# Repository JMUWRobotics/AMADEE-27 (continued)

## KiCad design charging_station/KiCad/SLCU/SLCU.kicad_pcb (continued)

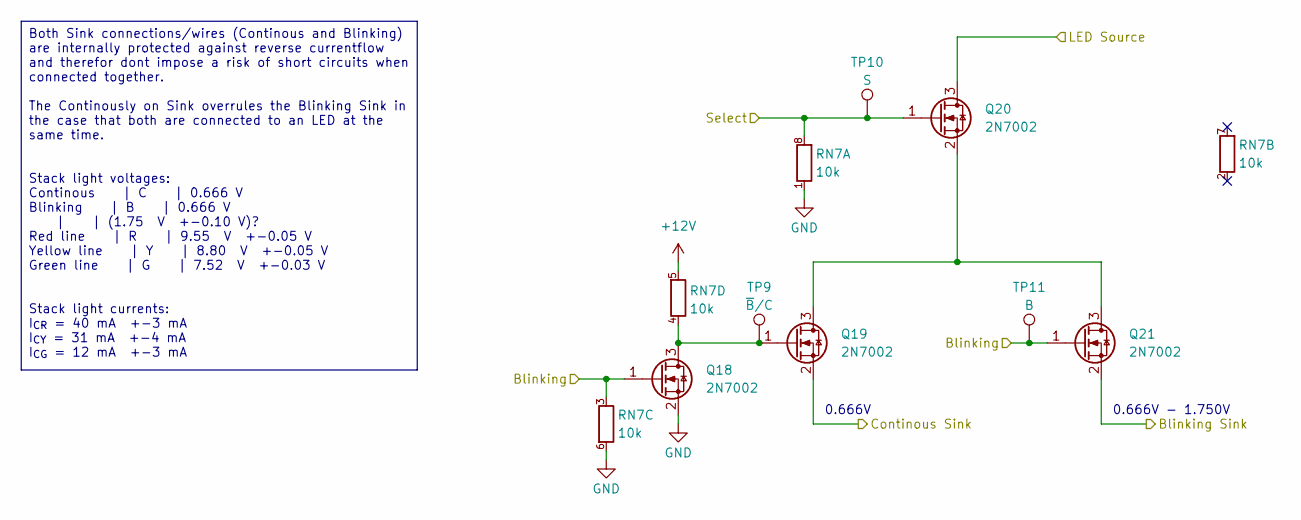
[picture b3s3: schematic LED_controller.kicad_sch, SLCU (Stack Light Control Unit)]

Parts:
Q18, Q19, Q20, Q21: 2N7002; SOT-323_SC-70
RN7: 10k; RES-ARRAY-SMD_0603-8P-L3.2-W1.6-BL; MPN 4D03WGJ0103T5E; LCSC Part C29718
TP9: ~{B}/C; TestPoint_Pad_D1.0mm
TP10: S; TestPoint_Pad_D1.0mm
TP11: B; TestPoint_Pad_D1.0mm

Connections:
+12V: RN7.5 (R4.2); also elsewhere on the board
/Blinking: Q21.2 (S); also elsewhere on the board
/Continous: Q19.2 (S); also elsewhere on the board
/Raspberry Signal & Logic Multiplexing/B_RED: Q18.1 (G), Q21.1 (G), RN7.3 (R3.1), TP11.1 (1_1); also elsewhere on the board
/Raspberry Signal & Logic Multiplexing/S_RED: Q20.1 (G), RN7.8 (R1.2), TP10.1 (1_1); also elsewhere on the board
/Red: Q20.3 (D); also elsewhere on the board
GND: Q18.2 (S), RN7.1 (R1.1), RN7.6 (R3.2); also elsewhere on the board
unnamed: Q18.3 (D), Q19.1 (G), RN7.4 (R4.1), TP9.1 (1_1)
unnamed: Q19.3 (D), Q20.2 (S), Q21.3 (D)

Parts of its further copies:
Q22, Q23, Q24, Q25, Q26, Q27, Q28, Q29: 2N7002; SOT-323_SC-70
RN8, RN9: 10k; RES-ARRAY-SMD_0603-8P-L3.2-W1.6-BL; MPN 4D03WGJ0103T5E; LCSC Part C29718
TP12, TP15: ~{B}/C; TestPoint_Pad_D1.0mm
TP13, TP16: S; TestPoint_Pad_D1.0mm
TP14, TP17: B; TestPoint_Pad_D1.0mm

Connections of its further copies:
+12V: RN8.5 (R4.2), RN9.5 (R4.2); also elsewhere on the board
/Blinking: Q25.2 (S), Q29.2 (S); also elsewhere on the board
/Continous: Q23.2 (S), Q27.2 (S); also elsewhere on the board
/Green: Q28.3 (D); also elsewhere on the board
/Green Light Driver/Blinking: Q26.1 (G), Q29.1 (G), RN9.3 (R3.1), TP17.1 (1_1); also elsewhere on the board
/Green Light Driver/Select: Q28.1 (G), RN9.8 (R1.2), TP16.1 (1_1); also elsewhere on the board
/Raspberry Signal & Logic Multiplexing/B_YELLOW: Q22.1 (G), Q25.1 (G), RN8.3 (R3.1), TP14.1 (1_1); also elsewhere on the board
/Raspberry Signal & Logic Multiplexing/S_YELLOW: Q24.1 (G), RN8.8 (R1.2), TP13.1 (1_1); also elsewhere on the board
/Yellow: Q24.3 (D); also elsewhere on the board
GND: Q22.2 (S), Q26.2 (S), RN8.1 (R1.1), RN8.6 (R3.2), RN9.1 (R1.1), RN9.6 (R3.2); also elsewhere on the board
unnamed: Q22.3 (D), Q23.1 (G), RN8.4 (R4.1), TP12.1 (1_1)
unnamed: Q23.3 (D), Q24.2 (S), Q25.3 (D)
unnamed: Q26.3 (D), Q27.1 (G), RN9.4 (R4.1), TP15.1 (1_1)
unnamed: Q27.3 (D), Q28.2 (S), Q29.3 (D)

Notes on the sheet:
0.666V
0.666V - 1.750V
Both Sink connections/wires (Continous and Blinking) are internally protected against reverse currentflow and therefor dont impose a risk of short circuits when connected together. The Continously on Sink overrules the Blinking Sink in the case that both are connected to an LED at the same time. St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

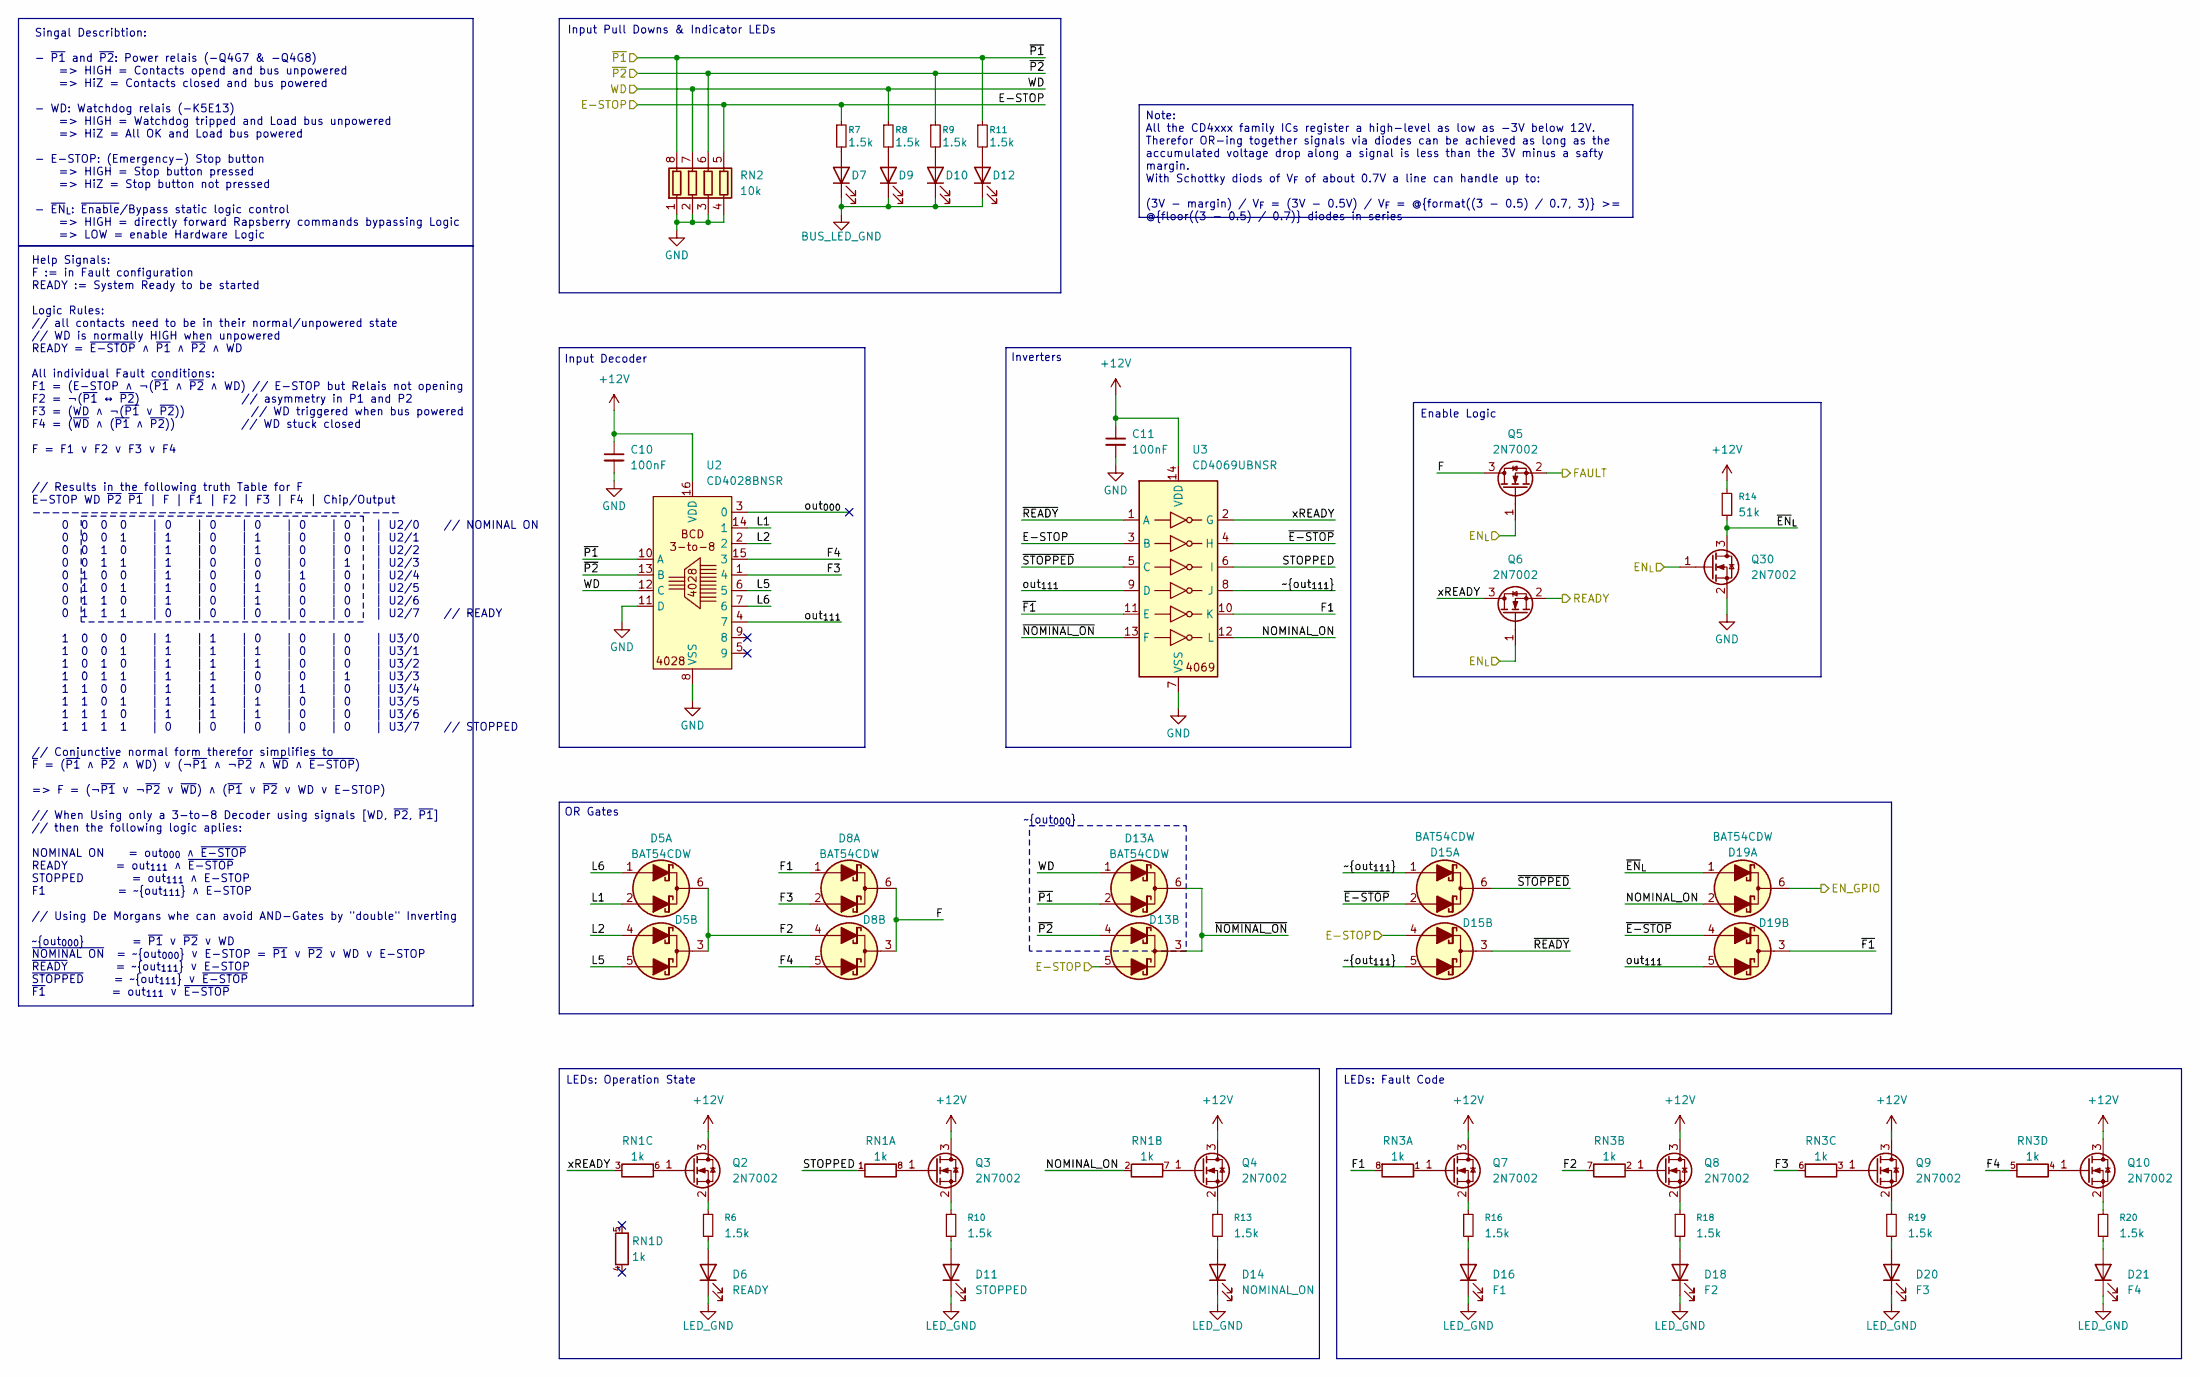
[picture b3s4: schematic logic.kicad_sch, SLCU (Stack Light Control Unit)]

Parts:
C10, C11: 100nF; C_0805_2012Metric_Pad1.18x1.45mm_HandSolder
D5, D8, D13, D15, D19: BAT54CDW; SOT-363_SC-70-6
D6: READY; LED_0805_2012Metric_Pad1.15x1.40mm_HandSolder
D7: E-STOP; LED_0805_2012Metric_Pad1.15x1.40mm_HandSolder
D9: WD; LED_0805_2012Metric_Pad1.15x1.40mm_HandSolder
D10: ~{P2}; LED_0805_2012Metric_Pad1.15x1.40mm_HandSolder
D11: STOPPED; LED_0805_2012Metric_Pad1.15x1.40mm_HandSolder
D12: ~{P1}; LED_0805_2012Metric_Pad1.15x1.40mm_HandSolder
D14: NOMINAL_ON; LED_0805_2012Metric_Pad1.15x1.40mm_HandSolder
D16: F1; LED_0805_2012Metric_Pad1.15x1.40mm_HandSolder
D18: F2; LED_0805_2012Metric_Pad1.15x1.40mm_HandSolder
D20: F3; LED_0805_2012Metric_Pad1.15x1.40mm_HandSolder
D21: F4; LED_0805_2012Metric_Pad1.15x1.40mm_HandSolder
Q2, Q3, Q4, Q5, Q6, Q7, Q8, Q9, Q10, Q30: 2N7002; SOT-323_SC-70
R6, R7, R8, R9, R10, R11, R13, R16, R18, R19, R20: 1.5k; R_0805_2012Metric_Pad1.20x1.40mm_HandSolder
R14: 51k; R_0805_2012Metric_Pad1.20x1.40mm_HandSolder
RN1, RN3: 1k; RES-ARRAY-SMD_0603-8P-L3.2-W1.6-BL; MPN 4D03WGJ0102T5E; LCSC Part C20197
RN2: 10k; RES-ARRAY-SMD_0603-8P-L3.2-W1.6-BL; MPN 4D03WGJ0103T5E; LCSC Part C29718
U2: CD4028BNSR; SOIC127P780X200-16N; MPN CD4028BNSR; LCSC Part C2869122
U3: CD4069UBNSR; SOIC127P780X200-14N; Mouser Part Number 595-CD4069UBNSR

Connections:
+12V: C10.1, C11.1, Q2.3 (D), Q3.3 (D), Q4.3 (D), Q7.3 (D), Q8.3 (D), Q9.3 (D), Q10.3 (D), R14.1, U2.16 (VDD), U3.14 (VDD); also elsewhere on the board
/E-STOP: D13.5 (A2), D15.4 (A2), R7.1, RN2.5 (R4.2), U3.3 (B); also elsewhere on the board
/Logic/EN_GPIO: D19.6 (K1); also elsewhere on the board
/Logic/EN_{L}: Q5.1 (G), Q6.1 (G), Q30.1 (G); also elsewhere on the board
/Logic/F: D8.3 (K2), D8.6 (K1), Q5.3 (D)
/Logic/F1: D8.1 (A1), RN3.8 (R1.2), U3.10 (K)
/Logic/F2: D5.3 (K2), D5.6 (K1), D8.4 (A2), RN3.7 (R2.2)
/Logic/F3: D8.2 (A1), RN3.6 (R3.2), U2.1 (4)
/Logic/F4: D8.5 (A2), RN3.5 (R4.2), U2.15 (3)
/Logic/FAULT: Q5.2 (S); also elsewhere on the board
/Logic/L1: D5.2 (A1), U2.14 (1)
/Logic/L2: D5.4 (A2), U2.2
/Logic/L5: D5.5 (A2), U2.6 (5)
/Logic/L6: D5.1 (A1), U2.7 (6)
/Logic/NOMINAL_ON: D19.2 (A1), RN1.2 (R2.1), U3.12 (L)
/Logic/READY: Q6.2 (S); also elsewhere on the board
/Logic/STOPPED: RN1.1 (R1.1), U3.6 (I)
/Logic/out_{000}: U2.3 (0)
/Logic/out_{111}: D19.5 (A2), U2.4 (7), U3.9 (D)
/Logic/xREADY: Q6.3 (D), RN1.3 (R3.1), U3.2 (G)
/Logic/~E-STOP: D15.2 (A1), D19.4 (A2), U3.4 (H)
/Logic/~EN_{L}: D19.1 (A1), Q30.3 (D), R14.2
/Logic/~F1: D19.3 (K2), U3.11 (E)
/Logic/~NOMINAL_ON: D13.3 (K2), D13.6 (K1), U3.13 (F)
/Logic/~READY: D15.3 (K2), U3.1 (A)
/Logic/~STOPPED: D15.6 (K1), U3.5 (C)
/Logic/~out_{111}: D15.1 (A1), D15.5 (A2), U3.8 (J)
/WD: D13.1 (A1), R8.1, RN2.7 (R2.2), U2.12 (C); also elsewhere on the board
/~P1: D13.2 (A1), R11.1, RN2.8 (R1.2), U2.10 (A); also elsewhere on the board
/~P2: D13.4 (A2), R9.1, RN2.6 (R3.2), U2.13 (B); also elsewhere on the board
BUS_LED_GND: D7.1 (K), D9.1 (K), D10.1 (K), D12.1 (K); also elsewhere on the board
GND: C10.2, C11.2, Q30.2 (S), RN2.1 (R1.1), RN2.2 (R2.1), RN2.3 (R3.1), RN2.4 (R4.1), U2.8 (VSS), U2.11 (D), U3.7 (VSS); also elsewhere on the board
LED_GND: D6.1 (K), D11.1 (K), D14.1 (K), D16.1 (K), D18.1 (K), D20.1 (K), D21.1 (K); also elsewhere on the board
unnamed: D6.2 (A), R6.2
unnamed: D7.2 (A), R7.2
unnamed: D9.2 (A), R8.2
unnamed: D10.2 (A), R9.2
unnamed: D11.2 (A), R10.2
unnamed: D12.2 (A), R11.2
unnamed: D14.2 (A), R13.2
unnamed: D16.2 (A), R16.2
unnamed: D18.2 (A), R18.2
unnamed: D20.2 (A), R19.2
unnamed: D21.2 (A), R20.2
unnamed: Q2.1 (G), RN1.6 (R3.2)
unnamed: Q2.2 (S), R6.1
unnamed: Q3.1 (G), RN1.8 (R1.2)
unnamed: Q3.2 (S), R10.1
unnamed: Q4.1 (G), RN1.7 (R2.2)
unnamed: Q4.2 (S), R13.1
unnamed: Q7.1 (G), RN3.1 (R1.1)
unnamed: Q7.2 (S), R16.1
unnamed: Q8.1 (G), RN3.2 (R2.1)
unnamed: Q8.2 (S), R18.1
unnamed: Q9.1 (G), RN3.3 (R3.1)
unnamed: Q9.2 (S), R19.1
unnamed: Q10.1 (G), RN3.4 (R4.1)
unnamed: Q10.2 (S), R20.1

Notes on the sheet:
Input Decoder
Enable Logic
~{out_{000}}
Help Signals: F := in Fault configuration READY := System Ready to be started Logic Rules: // all contacts need to be in their normal/unpowered state // WD is normally HIGH when unpowered READY = ~{E-STOP} ∧ ~{P1} ∧ ~{P2} ∧ WD All individual Fault conditions: F1 = (E-STOP ∧ ¬(~{P1} ∧ ~{P2} ∧ WD) //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
OR Gates
LEDs: Operation State
Singal Describtion: - ~{P1} and ~{P2}: Power relais (-Q4G7 & -Q4G8) => HIGH = Contacts opend and bus unpowered => HiZ = Contacts closed and bus powered - WD: Watchdog relais (-K5E13) => HIGH = Watchdog tripped and Load bus unpowered => HiZ = All OK and Load bus powered - E-STOP: (Emergency-) Stop b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
LEDs: Fault Code
Inverters
Input Pull Downs & Indicator LEDs
Note: All the CD4xxx family ICs register a high-level as low as -3V below 12V. Therefor OR-ing together signals via diodes can be achieved as long as the accumulated voltage drop along a signal is less than the 3V minus a safty margin. With Schottky diods of V_{F} of about 0.7V a line can handle up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

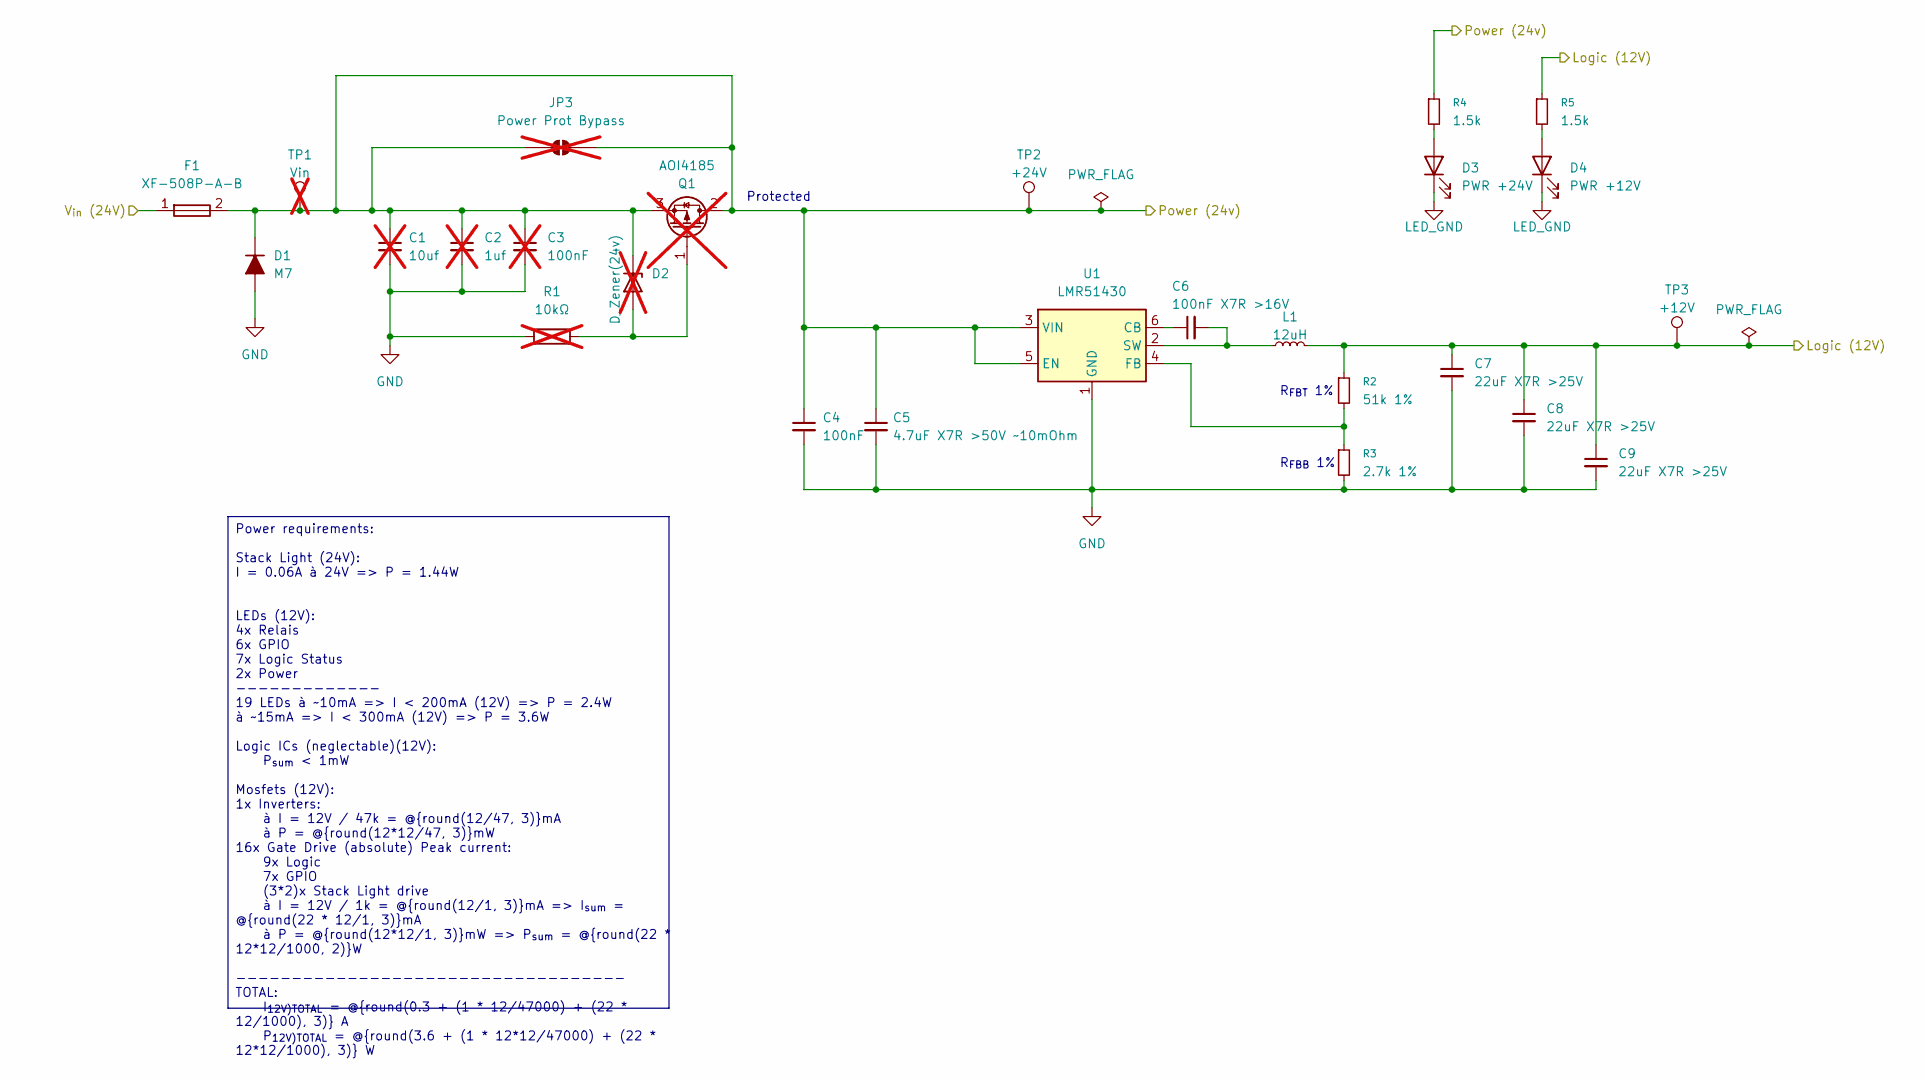
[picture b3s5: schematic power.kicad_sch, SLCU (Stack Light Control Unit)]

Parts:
C1: 10uf; C_0805_2012Metric; not fitted
C2: 1uf; C_0805_2012Metric; not fitted
C3: 100nF; C_0805_2012Metric; not fitted
C4: 100nF; C_0805_2012Metric_Pad1.18x1.45mm_HandSolder
C5: 4.7uF X7R >50V ~10mOhm; C_1206_3216Metric
C6: 100nF X7R >16V; C_0805_2012Metric
C7, C8, C9: 22uF X7R >25V; C_0805_2012Metric_Pad1.18x1.45mm_HandSolder
D1: M7; D_SMA
D2: D_Zener(24v); D_0805_2012Metric_Pad1.15x1.40mm_HandSolder; not fitted
D3: PWR +24V; LED_0805_2012Metric_Pad1.15x1.40mm_HandSolder
D4: PWR +12V; LED_0805_2012Metric_Pad1.15x1.40mm_HandSolder
F1: XF-508P-A-B; FUSE-TH_XF-508P-A-B; MPN XF-508P-A-B; LCSC Part C19727304
JP3: Power Prot Bypass; SolderJumper-2_P1.3mm_Open_RoundedPad1.0x1.5mm; not fitted
L1: 12uH; L_12x12mm_H8mm; MPN CDRH127NP-120MC; LCSC Part C338772
Q1: AOI4185; TO-251-3_Vertical; not fitted
R1: 10kΩ; R_0805_2012Metric_Pad1.20x1.40mm_HandSolder; not fitted
R2: 51k 1%; R_0805_2012Metric_Pad1.20x1.40mm_HandSolder
R3: 2.7k 1%; R_0805_2012Metric_Pad1.20x1.40mm_HandSolder
R4, R5: 1.5k; R_0805_2012Metric_Pad1.20x1.40mm_HandSolder
TP1: Vin; TestPoint_Pad_D1.5mm; not fitted
TP2: +24V; TestPoint_Pad_D1.5mm
TP3: +12V; TestPoint_Pad_D1.5mm
U1: LMR51430; SOT-23-6

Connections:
+12V: C7.1, C8.1, C9.1, L1.2, R2.1, R5.1, TP3.1 (1_1); also elsewhere on the board
+24V: C1.1, C2.1, C3.1, C4.1, C5.1, D1.1 (K), D2.1 (K), F1.2, JP3.1 (A), JP3.2 (B), Q1.2 (D), Q1.3 (S), R4.1, TP1.1, TP2.1 (1_1), U1.3 (VIN), U1.5 (EN); also elsewhere on the board
/Power/V_{in} (24V): F1.1; also elsewhere on the board
GND: C1.2, C2.2, C3.2, C4.2, C5.2, C7.2, C8.2, C9.2, D1.2 (A), R1.2, R3.2, U1.1 (GND); also elsewhere on the board
LED_GND: D3.1 (K), D4.1 (K); also elsewhere on the board
unnamed: D2.2 (A), Q1.1 (G), R1.1
unnamed: D3.2 (A), R4.2
unnamed: D4.2 (A), R5.2
unnamed: C6.1, U1.6 (CB)
unnamed: R2.2, R3.1, U1.4 (FB)
unnamed: C6.2, L1.1, U1.2 (SW)

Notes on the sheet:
Protected
R_{FBT} 1%
R_{FBB} 1%
Power requirements: Stack Light (24V): I = 0.06A à 24V => P = 1.44W LEDs (12V): 4x Relais 6x GPIO 7x Logic Status 2x Power ------------- 19 LEDs à ~10mA => I < 200mA (12V) => P = 2.4W à ~15mA => I < 300mA (12V) => P = 3.6W Logic ICs (neglectable)(12V): P_{sum} < 1mW Mosfets (12V): 1x Inverters: à I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

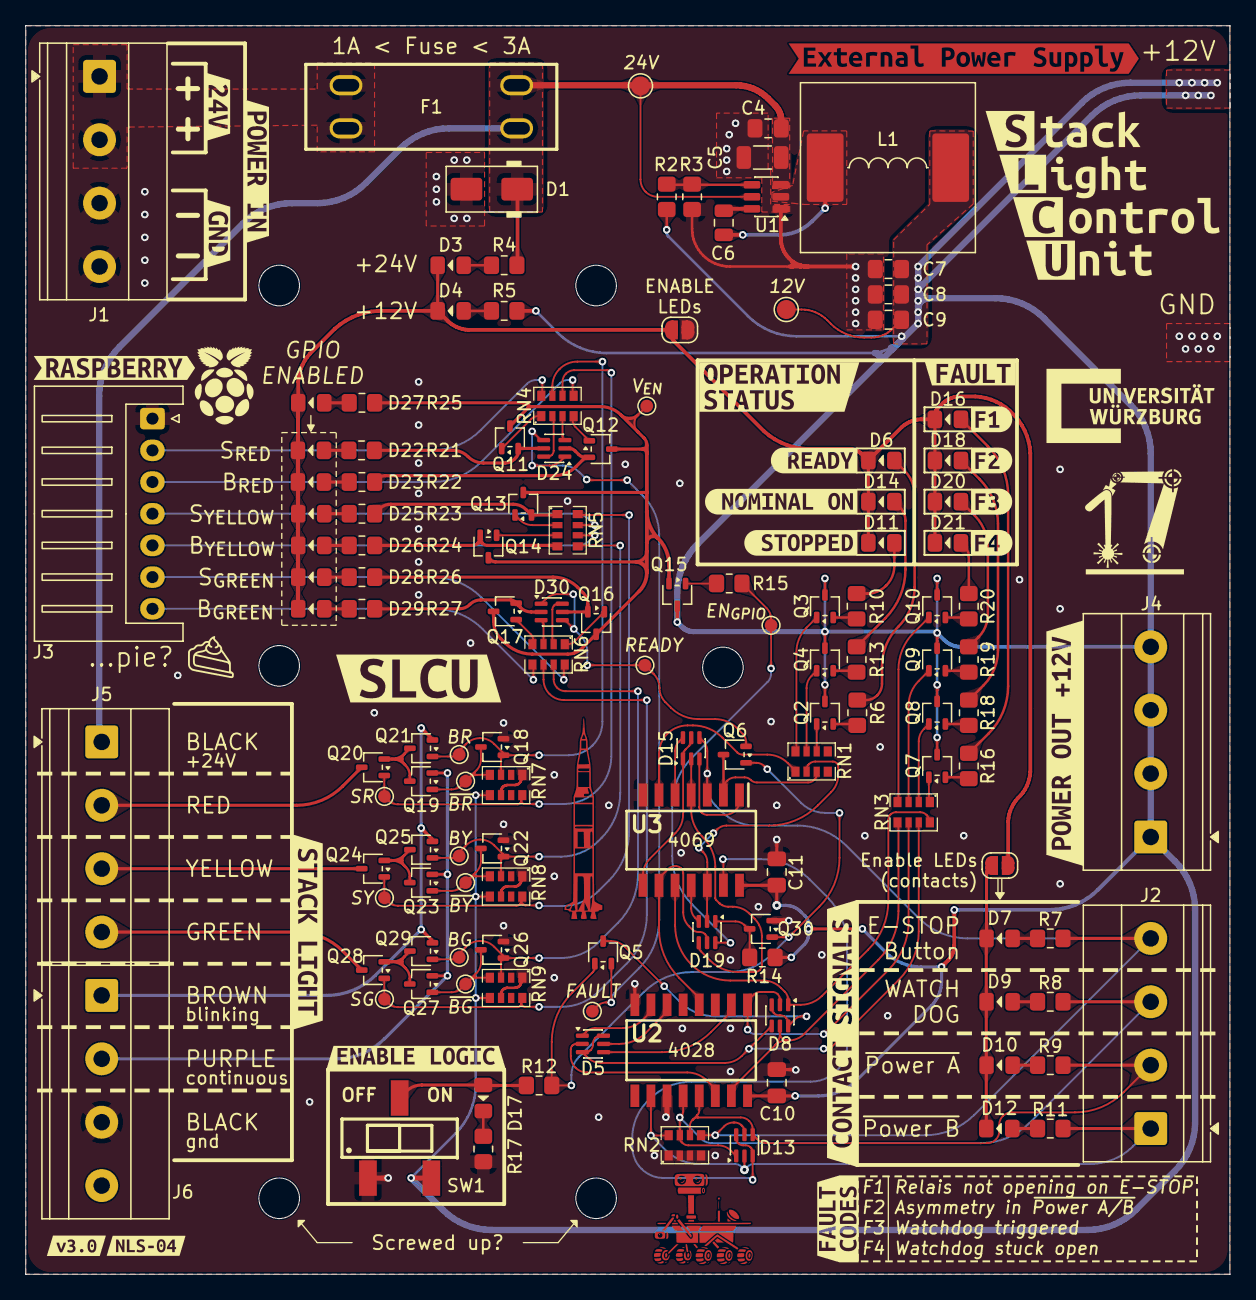
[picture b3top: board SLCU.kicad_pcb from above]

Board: 2 copper layers, 95.0 x 98.5 mm, 167 parts (0 on the bottom side), 114 nets.

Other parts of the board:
kibuzzard-6ACFD3B4: G***; kibuzzard-6ACFD3B4
kibuzzard-6ACFD63A: G***; kibuzzard-6ACFD63A
kibuzzard-6ACFD560: G***; kibuzzard-6ACFD560
kibuzzard-6ACFDAEA: G***; kibuzzard-6ACFDAEA
kibuzzard-6ACFDB30: G***; kibuzzard-6ACFDB30
kibuzzard-6ACFDB37: G***; kibuzzard-6ACFDB37
kibuzzard-6ACFDC5F: G***; kibuzzard-6ACFDC5F
kibuzzard-6ACFDC7C: G***; kibuzzard-6ACFDC7C
kibuzzard-6ACFDC65: G***; kibuzzard-6ACFDC65
kibuzzard-6ACFDC83: G***; kibuzzard-6ACFDC83
kibuzzard-6ACFDD22: G***; kibuzzard-6ACFDD22
kibuzzard-6ACFDD51: G***; kibuzzard-6ACFDD51
kibuzzard-6ACFDDC7: G***; kibuzzard-6ACFDDC7
kibuzzard-6ACFDE5B: G***; kibuzzard-6ACFDE5B
kibuzzard-6ACFDF9B: G***; kibuzzard-6ACFDF9B
kibuzzard-6ACFDF9F: G***; kibuzzard-6ACFDF9F
kibuzzard-6ACFDF95: G***; kibuzzard-6ACFDF95
kibuzzard-6ACFDFA3: G***; kibuzzard-6ACFDFA3
kibuzzard-6ACFDFAE: G***; kibuzzard-6ACFDFAE
kibuzzard-6ACFDFB1: G***; kibuzzard-6ACFDFB1
kibuzzard-6ACFDFBD: G***; kibuzzard-6ACFDFBD
kibuzzard-6ACFDFF0: G***; kibuzzard-6ACFDFF0
kibuzzard-6ACFE1C2: G***; kibuzzard-6ACFE1C2
kibuzzard-6ACFE19D: G***; kibuzzard-6ACFE19D
kibuzzard-6ACFE193: G***; kibuzzard-6ACFE193
kibuzzard-6ACFE465: G***; kibuzzard-6ACFE465
kibuzzard-6AD001C0: G***; kibuzzard-6AD001C0
kibuzzard-6AD01D0B: G***; kibuzzard-6AD01D0B
kibuzzard-6AD0072F: G***; kibuzzard-6AD0072F
kibuzzard-6AD0073C: G***; kibuzzard-6AD0073C
kibuzzard-6AD00824: G***; kibuzzard-6AD00824

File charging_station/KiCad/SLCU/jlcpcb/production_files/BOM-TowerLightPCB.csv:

Comment,Designator,Footprint,LCSC,Quantity
1.5k,"R10,R11,R12,R13,R15,R16,R17,R18,R19,R20,R21,R22,R23,R24,R25,R26,R27,R4,R5,R6,R7,R8,R9",R_0805_2012Metric_Pad1.20x1.40mm_HandSolder,C4310,23
100n,"C10,C11,C4",C_0805_2012Metric_Pad1.18x1.45mm_HandSolder,C49678,3
100nF X7R >16V,C6,C_0805_2012Metric,C49678,1
10k,"RN2,RN7,RN8,RN9",RES-ARRAY-SMD_0603-8P-L3.2-W1.6-BL,C29718,4
12uH,L1,L_12x12mm_H8mm,C338772,1
1k,"RN1,RN3,RN4,RN5,RN6",RES-ARRAY-SMD_0603-8P-L3.2-W1.6-BL,C20197,5
2.7k 1%,R3,R_0805_2012Metric_Pad1.20x1.40mm_HandSolder,C17530,1
22uF X7R >25V,"C7,C8,C9",C_0805_2012Metric_Pad1.18x1.45mm_HandSolder,C45783,3
2N7002,"Q10,Q11,Q12,Q13,Q14,Q15,Q16,Q17,Q18,Q19,Q2,Q20,Q21,Q22,Q23,Q24,Q25,Q26,Q27,Q28,Q29,Q3,Q30,Q4,Q5,Q6,Q7,Q8,Q9",SOT-323_SC-70,C7420322,29
4.7uF X7R >50V ~10mOhm,C5,C_1206_3216Metric,C29823,1
51k,R14,R_0805_2012Metric_Pad1.20x1.40mm_HandSolder,C17737,1
51k 1%,R2,R_0805_2012Metric_Pad1.20x1.40mm_HandSolder,C17737,1
BAT54CDW,"D13,D15,D19,D24,D30,D5,D8",SOT-363_SC-70-6,C49190672,7
CD4028BNSR,U2,SOIC127P780X200-16N,C131484,1
CD4069UBNSR,U3,SOIC127P780X200-14N,C2866535,1
Contact Signals,J2,"TerminalBlock_Phoenix_MKDS-1,5-4_1x04_P5.00mm_Horizontal",C3817931,1
E-STOP,D7,LED_0805_2012Metric_Pad1.15x1.40mm_HandSolder,C84256,1
EN_LOGIC,D17,LED_0805_2012Metric_Pad1.15x1.40mm_HandSolder,C2297,1
Enable Logic,SW1,SW-SMD_SHOUHAN_MST-22D18G23J_C2875122,C2875122,1
F1,D16,LED_0805_2012Metric_Pad1.15x1.40mm_HandSolder,C84256,1
F2,D18,LED_0805_2012Metric_Pad1.15x1.40mm_HandSolder,C84256,1
F3,D20,LED_0805_2012Metric_Pad1.15x1.40mm_HandSolder,C84256,1
F4,D21,LED_0805_2012Metric_Pad1.15x1.40mm_HandSolder,C84256,1
Input Power (24V),J1,"TerminalBlock_Phoenix_MKDS-1,5-4_1x04_P5.00mm_Horizontal",C3817931,1
LED,"D25,D26",LED_0805_2012Metric_Pad1.15x1.40mm_HandSolder,C2296,2
LED,"D27,D28,D29",LED_0805_2012Metric_Pad1.15x1.40mm_HandSolder,C2297,3
LED,"D22,D23",LED_0805_2012Metric_Pad1.15x1.40mm_HandSolder,C84256,2
LMR51430,U1,SOT-23-6,C5185863,1
Logic Power Out,J4,"TerminalBlock_Phoenix_MKDS-1,5-4_1x04_P5.00mm_Horizontal",C3817931,1
M7,D1,D_SMA,C95872,1
NOMINAL_ON,D14,LED_0805_2012Metric_Pad1.15x1.40mm_HandSolder,C2297,1
PWR +12V,D4,LED_0805_2012Metric_Pad1.15x1.40mm_HandSolder,C2297,1
PWR +24V,D3,LED_0805_2012Metric_Pad1.15x1.40mm_HandSolder,C2297,1
READY,D6,LED_0805_2012Metric_Pad1.15x1.40mm_HandSolder,C2297,1
Raspberry Control Signals,J3,JST_XH_S7B-XH-A_1x07_P2.50mm_Horizontal,C157916,1
STOPPED,D11,LED_0805_2012Metric_Pad1.15x1.40mm_HandSolder,C2297,1
Stack Light DOWN,J6,"TerminalBlock_Phoenix_MKDS-1,5-4_1x04_P5.00mm_Horizontal",C3817931,1
Stack Light UP,J5,"TerminalBlock_Phoenix_MKDS-1,5-4_1x04_P5.00mm_Horizontal",C3817931,1
WD,D9,LED_0805_2012Metric_Pad1.15x1.40mm_HandSolder,C84256,1
XF-508P-A-B,F1,FUSE-TH_XF-508P-A-B,C19727304,1
~{P1},D12,LED_0805_2012Metric_Pad1.15x1.40mm_HandSolder,C84256,1
~{P2},D10,LED_0805_2012Metric_Pad1.15x1.40mm_HandSolder,C84256,1

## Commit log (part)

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2026-04-27 init readme
2026-04-27 license init
    MIT ? double check later
2026-06-23 charging station: add initial dpm86 api
2026-06-23 charging station: updated ansi coloring
2026-06-23 charging station: move api
2026-06-23 charging station: simple test
